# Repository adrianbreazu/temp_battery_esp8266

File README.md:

# temp_battery_esp8266

#About

This is a simple ESP8266-01 project that measures the temperature every 30 minutes (can be easily adjusted from the code) and sends to a web server using POST requests.
To enable access to WWW add DNS to the code

#Hardware requirements

* ESP8266-01 (make sure you manually enable the deepsleep - requires soldering see youtube videos)
* 4 capacitors
* MCP1700 3.3 voltage regulator LDO
* 2 resistors
* 1 ds18b20 temperature sensor
* pcb board and connectors

# Software requirements

* Web server
* clone this repository
* ARduino IDe and ESP8266 board added

#Images

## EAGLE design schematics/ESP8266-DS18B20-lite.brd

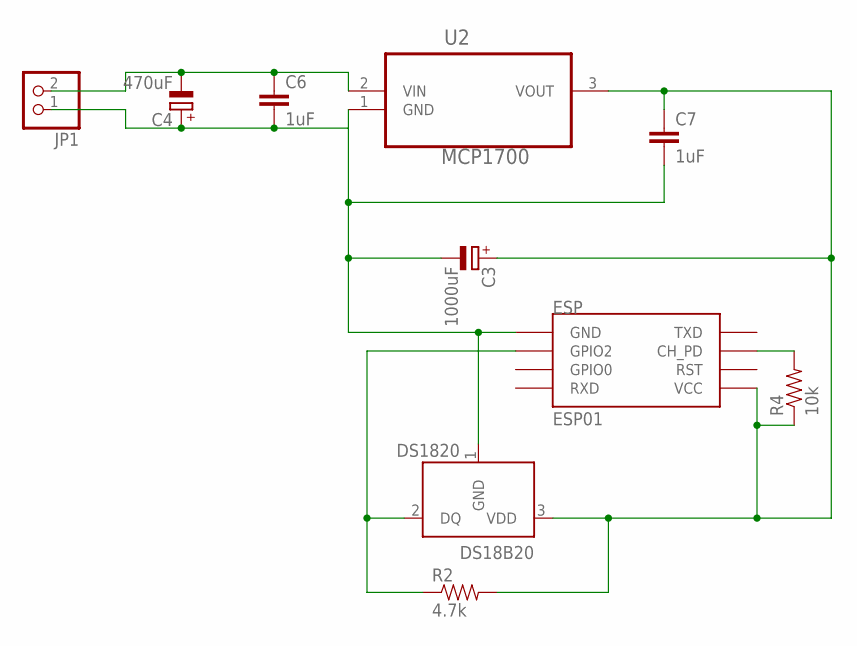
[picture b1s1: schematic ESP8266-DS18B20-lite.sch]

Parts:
C3: 1000uF; E2,5-5
C4: 470uF; E2,5-5
C6, C7: 1uF; CAP-PTH-SMALLEZ
DS18B20: DS1820; TO-92
ESP: ESP01
JP1: PINHD-1X2/90; 1X02/90
R2: 4.7k; AXIAL-0.3
R4: 10k; AXIAL-0.3
U2: MCP1700; TO127P254X495-3

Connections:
3V3: C3.+, C7.1, DS18B20.3 (VDD), ESP.VCC, R2.P$2 (2), R4.P$1 (1), U2.3 (VOUT)
6.2V: C4.-, C6.1, JP1.2, U2.2 (VIN)
CH: ESP.CH_PD, R4.P$2 (2)
DQ: DS18B20.2 (DQ), ESP.GPIO2, R2.P$1 (1)
GND: C3.-, C4.+, C6.2, C7.2, DS18B20.1 (GND), ESP.GND, JP1.1, U2.1 (GND)

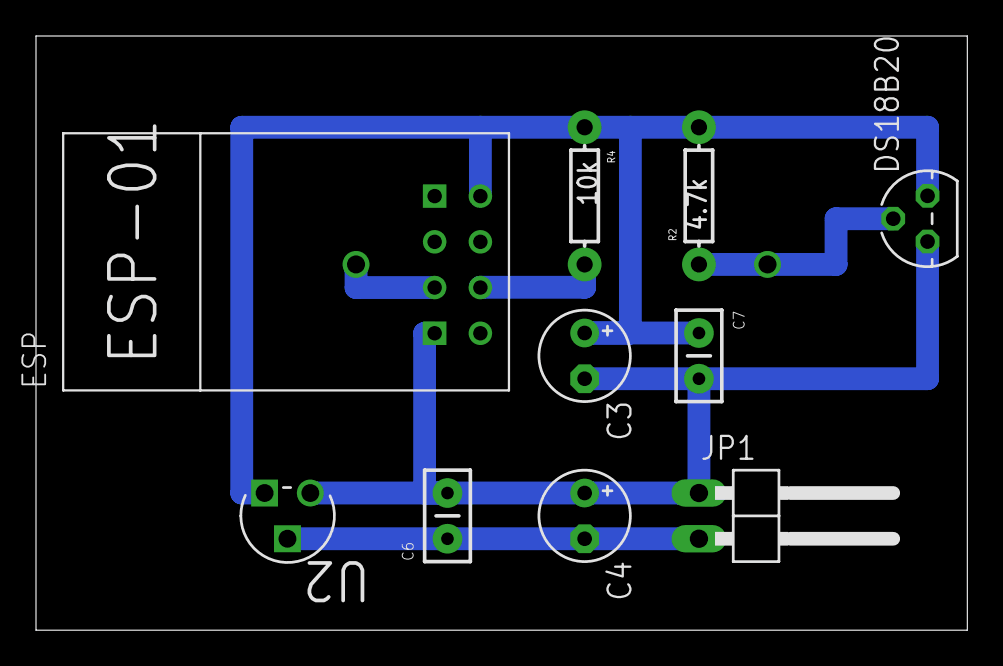
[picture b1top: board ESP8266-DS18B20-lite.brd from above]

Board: 2 copper layers, 51.7 x 33.0 mm, 10 parts (0 on the bottom side), 5 nets.

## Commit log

2018-07-18 ds18b20 sensor code, POST request sent from ESP to a web server
2018-07-18 EACGLE schematics
2018-07-18 add images

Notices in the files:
parts and their libraries:
SparkFun-Capacitors: Licensing: Creative Commons ShareAlike 4.0 International - https://creativecommons.org/licenses/by-sa/4.0
